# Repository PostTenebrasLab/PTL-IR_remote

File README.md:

# PTL IR remote

PTL IR remote is a wemos shield with sensors and actuators.

## Sensors / Actuators

 * IR leds
 * IR receiver
 * DHT22 temperature/humidity
 * brithness (photoresistor)
 * optional ds18b20 termometer (or any OneWire perif)
 * optional bme280 temperature/humidity/pressure

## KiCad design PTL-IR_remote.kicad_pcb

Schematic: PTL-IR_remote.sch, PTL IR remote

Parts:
C1: 100n; C_0603_1608Metric_Pad1.05x0.95mm_HandSolder
D1, D2: IR204A; LED_D5.0mm_IRGrey
D3: DIODE; D_PowerDI-123
D4: WS2813; LED_WS2812_PLCC6_5.0x5.0mm_P1.6mm
DHT22: DHT22; PinHeader_1x04_P2.54mm_Vertical
J1, J2: 8p; PinHeader_1x08_P2.54mm_Vertical
J4: Conn_01x03_Female; PinHeader_1x03_P2.54mm_Vertical
JP1: Jumper; solder-jumper-2
PR1: PHOTO (1MΩ); R_LDR_4.9x4.2mm_P2.54mm_Vertical
Q1: 2N7002; SOT-23
R1: 1kΩ (10kΩ); R_0805_2012Metric
R2: 22Ω; R_0805_2012Metric
R4: 220Ω; R_0805_2012Metric
R5: 4.7kΩ; R_0805_2012Metric
U1: TSOP4838; Vishay_MINIMOLD-3Pin
bme280: bme280; PinHeader_1x04_P2.54mm_Vertical

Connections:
+3V3: DHT22.1, J1.1, J4.2, PR1.1, R4.1, R5.2, bme280.4
+5V: D2.2 (A), D3.1, J2.8
DHT: DHT22.2, J2.3, JP1.1
GNDREF: C1.2, D4.5, DHT22.4, J2.7, J4.1, Q1.2 (S), R1.2, U1.2 (GND), bme280.3
IR: J2.5, Q1.1 (G)
IRM: J1.5, U1.1 (OUT)
unnamed: C1.1, R4.2, U1.3 (Vs)
unnamed: D1.1 (K), R2.1
unnamed: D1.2 (A), D2.1 (K)
unnamed: D3.2, D4.1
unnamed: JP1.2, bme280.2
unnamed: Q1.3 (D), R2.2
OneW: J1.4, J4.3, R5.1
PhR: J1.7, PR1.2, R1.1
RGB: D4.4, J2.6
SDA: J2.4, bme280.1

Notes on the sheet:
(5V-0.7V)*0.7 = 3.01V Din < 3.01V ;-)
Optional DS18B20 (one wire)
Optional I2C (bme280)
IR receiver
Thermometer
Wemos headers
RGB
brightness
IR transmitter
SCL

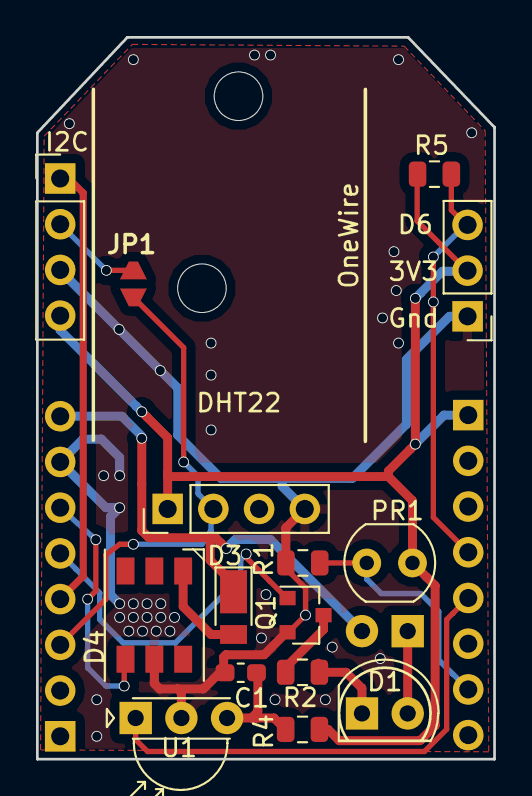
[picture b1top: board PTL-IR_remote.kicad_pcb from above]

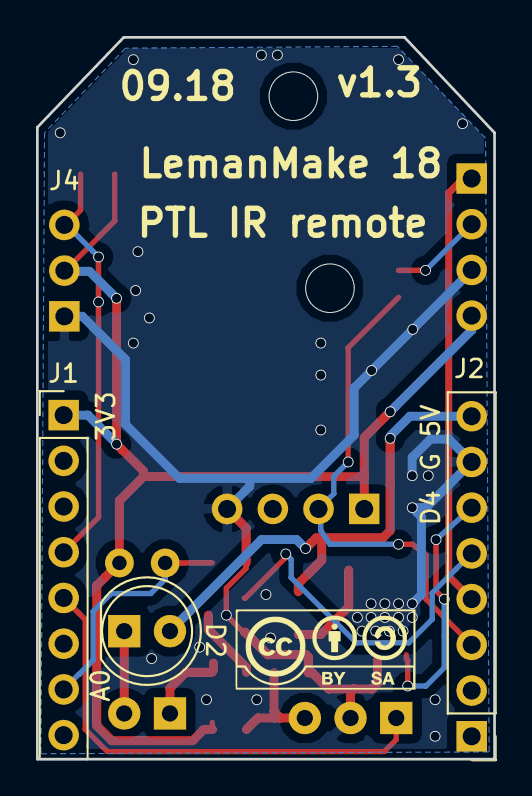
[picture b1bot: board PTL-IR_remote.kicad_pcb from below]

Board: 2 copper layers, 25.4 x 40.1 mm, 18 parts (3 on the bottom side), 16 nets.

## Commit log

2018-07-26 add correction notes on schema
2018-07-26 anotate schema modifs
2018-07-28 fix pcb v1.0 (and update to kicad v5)
2018-07-28 split schema
2018-07-28 first PCB (pcbway)
2018-07-28 change dir structure
2018-07-28 update gerber files
2018-07-28 minor changes
2018-07-28 remove unused dir
2018-07-28 update plot for v1.1-pre
2018-07-29 change diode footprint and reroute
2018-07-29 Create LICENSE
2018-07-29 add 3d componants and replot
2018-07-29 add readme
2018-07-30 add openscad wemos case (.stl)
2018-07-30 change led pin (D2), add jumper (bme280)
2018-08-02 replace OneWIre pads by 2.54 header
2018-08-02 update images
2018-08-16 Moved to Kicad5 Fixed swap of 5V and GND PCB is now V1.2
2018-09-02 Fixed missing mounting holes and PTL and CC logo. Added a few missing files...
2018-09-02 add soldering support and update case (3dprinting)
2018-09-02 forgot to add some modified files
2018-09-09 add PTL IR remote shield test sketch
2018-09-09 refactor serial test printout
2018-09-21 add makefile
2018-09-21 add mqtt support in test mode
2018-09-21 change mqtt test namespace
2018-09-21 fix OTA server url
2018-09-22 add precompiled test firmwares for OTA
2018-09-22 update precompiled test firmwares
2018-09-22 add first draft presentation
2018-09-22 update npm, fix vulnerabilities
2018-09-22 add sync_OTA in makefile
2018-09-23 first version firmware prod
2018-09-23 add index.html,/ir,/led pages
2018-09-23 move rewrite web page buffer into index.html handler
2018-09-24 add v3 firmwares
2018-09-24 add presentation links
2018-09-26 add small remote IR code
2018-09-26 add change IR led color
2018-09-27 add remote to led functions
2018-09-27 typo in presentation
2018-09-27 fix IRsend begin
2018-09-27 Changed beahviour to use AJAX for refresh each HTML files now has its own JS file
2018-09-28 update firmwares final version
2018-09-29 remove debug from final firmwares
